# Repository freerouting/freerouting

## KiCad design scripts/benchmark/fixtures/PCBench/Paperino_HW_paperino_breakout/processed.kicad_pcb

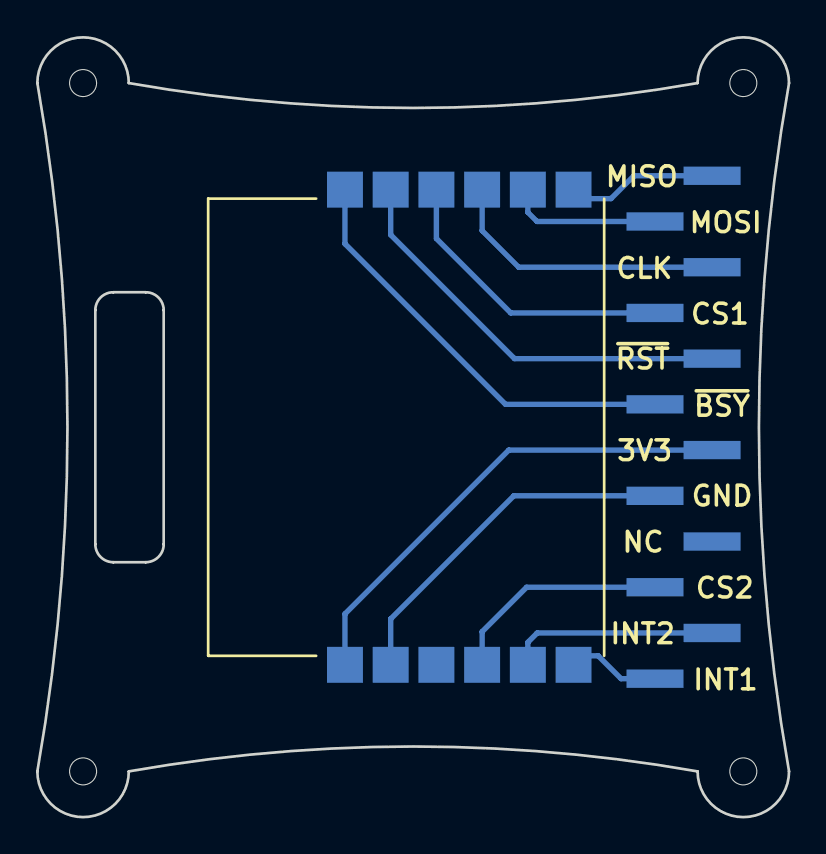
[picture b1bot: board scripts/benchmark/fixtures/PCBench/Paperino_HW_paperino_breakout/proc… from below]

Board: 2 copper layers, 41.8 x 43.3 mm, 6 parts (2 on the bottom side), 11 nets.

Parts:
A1: paperino_module
M1, M2, M3, M4: Mounting_hole; mounting_hole_1.5
X1: CONN_01X12; header_1x12_SMT

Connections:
+3V3: A1.1, X1.6
/CLK: A1.9, X1.10
/CS1: A1.10, X1.9
/CS2: A1.4, X1.3
/INT1: A1.6, X1.1
/INT2: A1.5, X1.2
/MISO: A1.7, X1.12
/MOSI: A1.8, X1.11
/~BSY: A1.12, X1.7
/~RST: A1.11, X1.8
GND: A1.2, X1.5

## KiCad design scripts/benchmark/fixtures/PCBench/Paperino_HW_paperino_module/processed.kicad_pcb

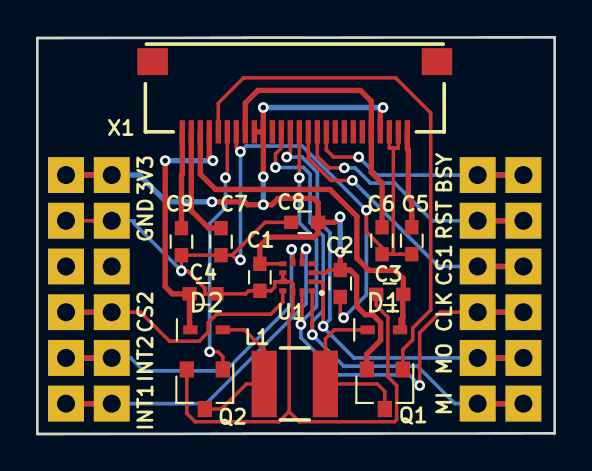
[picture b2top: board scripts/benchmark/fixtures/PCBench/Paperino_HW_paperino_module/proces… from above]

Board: 2 copper layers, 28.7 x 22.0 mm, 20 parts (0 on the bottom side), 21 nets.

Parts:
C1, C2, C5: 100n; C_0603
C3, C4: 2µ2; C_0603
C6, C7, C8, C9: 1µ; C_0603
D1, D2: 30V; SOD-523F
L1: 47µ; NR4018T470M
P1, P2, P3, P4: CONN_01X06; 1x6_header
Q1: PMOS; SOT-23
Q2: NMOS; SOT-23
U1: BMA250E; LGA-12-2x2x0.95
X1: XF2M-2615-1A

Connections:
+3V3: C1.1, C2.2, C8.1, P2.1, P4.1, Q1.2, U1.3, U1.7, X1.4, X1.17, X1.18
/GDR_N: Q2.1, X1.21
/GDR_P: Q1.1, X1.22
/INT1: P2.6, P4.6, U1.5
/INT2: P2.5, P4.5, U1.6
/SPI_CLK: P1.3, P3.3, U1.12, X1.13
/SPI_CS1: P1.4, P3.4, X1.12
/SPI_CS2: P2.4, P4.4, U1.10
/SPI_MISO: P1.1, P3.1, U1.1, X1.15
/SPI_MOSI: P1.2, P3.2, U1.2, X1.14
/TPCOM: C5.1, X1.1
/VDD: C6.1, X1.5, X1.19
/VGH: C4.2, D2.1, X1.23
/VGL: C3.1, D1.2, X1.24
/VSH: C7.1, X1.25
/VSL: C9.1, X1.26
/~BUSY: P1.6, P3.6, X1.10
/~RST: P1.5, P3.5, X1.11
GND: C1.2, C2.1, C3.2, C4.1, C5.2, C6.2, C7.2, C8.2, C9.2, P2.2, P4.2, Q2.2, U1.8, U1.9, U1.11, X1.2, X1.3, X1.20
unnamed: D1.1, L1.1, Q1.3
unnamed: D2.2, L1.2, Q2.3

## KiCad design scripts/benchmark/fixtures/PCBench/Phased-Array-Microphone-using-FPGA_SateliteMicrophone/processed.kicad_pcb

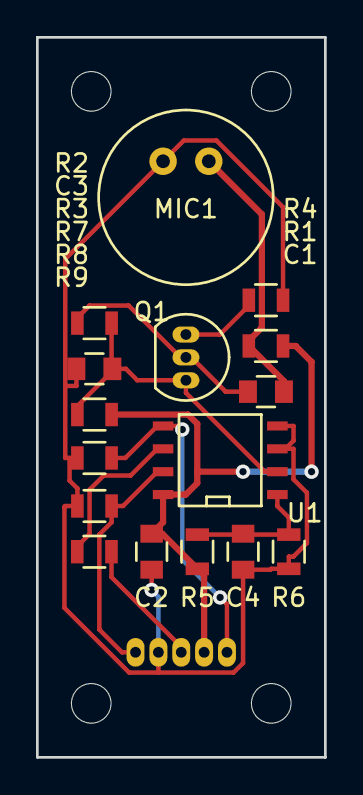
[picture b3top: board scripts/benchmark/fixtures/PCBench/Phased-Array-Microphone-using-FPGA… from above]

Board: 2 copper layers, 16.0 x 40.0 mm, 17 parts (0 on the bottom side), 11 nets.

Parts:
C1, C2, C4: 1uF; C_0805
C3: 1nF; C_0805
MIC1: CONN_02X01; Microphone9.7mm
P1: CONN_01X05; direct_ribbon_01x05
Q1: C945; TO-92_Inline_Narrow_Oval
R1, R3, R6: 10k; R_0805
R2: 100k; R_0805
R4: 20R; R_0805
R5: 15k; R_0805
R7, R8: 1k; R_0805
R9: 100R; R_0805
U1: LC549C; SOIC-8-N

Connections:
//CS: P1.5, R7.1, U1.5
/Ampout: C3.2, Q1.3, R2.1, R3.2, U1.2
/CLK: P1.1, R8.1, U1.7
/DATA: P1.3, R9.1
/Vref: C4.2, R5.2, R6.1, U1.1
GND: C2.1, C3.1, C4.1, MIC1.2, P1.2, R4.2, R6.2, R7.2, R8.2, U1.3, U1.4
unnamed: C1.1, Q1.2, R2.2
unnamed: C1.2, MIC1.1, R1.2
unnamed: Q1.1, R4.1
unnamed: R9.2, U1.6
VCC: C2.2, P1.4, R1.1, R3.1, R5.1, U1.8
